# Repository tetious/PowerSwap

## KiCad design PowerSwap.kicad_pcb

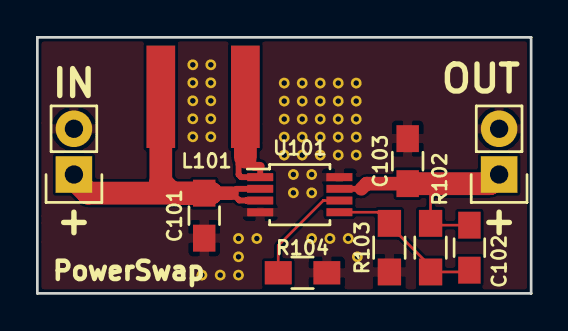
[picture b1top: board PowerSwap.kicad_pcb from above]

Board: 2 copper layers, 27.4 x 14.2 mm, 10 parts (0 on the bottom side), 6 nets.

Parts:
C101: 10uf; C_0805_HandSoldering
C102: NP; C_0805_HandSoldering
C103: 22uf; C_0805_HandSoldering
L101: 2.2uH; ASPI-0628
P101: IN; Pin_Header_Straight_1x02
P103: OUT; Pin_Header_Straight_1x02
R102: 750k; R_0805_HandSoldering
R103: 100k; R_0805_HandSoldering
R104: NP; R_0805_HandSoldering
U101: PAM2401; MSOP-8_3x3mm_Pitch0.65mm

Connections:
/Vin: C101.1, L101.1, P101.1, U101.2, U101.3
/Vout: C102.1, C103.1, P103.1, R102.1, U101.7
GND: C101.2, C103.2, P101.2, P103.2, R103.2, R104.2, U101.4, U101.8
unnamed: C102.2, R102.2, R103.1, U101.5
unnamed: L101.2, U101.1
unnamed: R104.1, U101.6

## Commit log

2016-08-12 Initial checkin.
2016-08-14 Cleanups.
